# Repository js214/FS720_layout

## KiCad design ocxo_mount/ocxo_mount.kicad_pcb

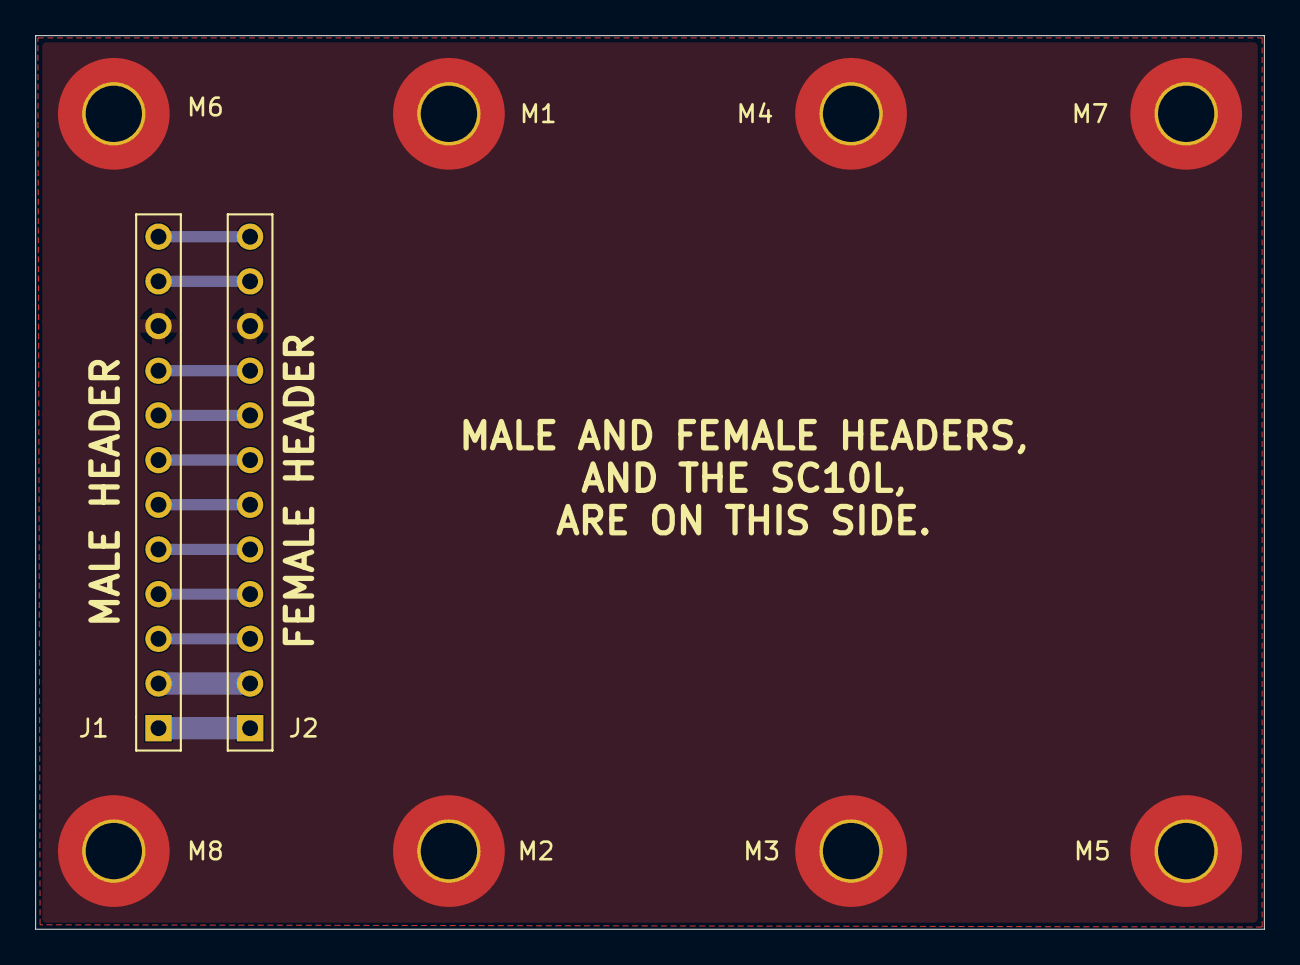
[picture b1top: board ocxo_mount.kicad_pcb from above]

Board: 2 copper layers, 69.8 x 50.8 mm, 10 parts (0 on the bottom side), 12 nets.

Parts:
J1: 12POS 2.54mm; HDR1X12
J2: Conn_01x12; HDR1X12
M1, M2, M3, M4, M5, M6, M7, M8: MountingPad_4-40; Hole_4-40

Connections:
/10MHZ_SINE_OUT: J1.6, J2.6
/10MHZ_SINE_RETURN: J1.7, J2.7
/+5.00VREF_OUT: J1.8, J2.8
/+24VDC: J1.1, J2.1
/AGC_MONITOR: J1.5, J2.5
/AMPL_CTL_IN: J1.11, J2.11
/FREQ_CTL_IN: J1.9, J2.9
/HEATER_POWER_MONITOR: J1.3, J2.3
/POWER_GND: J1.2, J2.2
/TEMP_CTL_IN: J1.12, J2.12
/VARACTOR_MONITOR: J1.4, J2.4
GND: J1.10, J2.10, M1.1 (1_1), M2.1 (1_1), M3.1 (1_1), M4.1 (1_1), M5.1 (1_1), M6.1 (1_1), M7.1 (1_1), M8.1 (1_1)

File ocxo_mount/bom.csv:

"Reference","Qty","Value","DNP","Exclude from BOM","Exclude from Board","Footprint","Datasheet","JLCPCB","SRS PN"
"J1","1","12POS 2.54mm","","","","CONNECTOR_SRS:HDR1X12","","","1-01541"
"J2","1","Conn_01x12","","","","CONNECTOR_SRS:HDR1X12","","","1-01602"
"PCB101","1","PCB","","","Excluded from board","","","--",""
"SC1,SC2,SC3,SC4,SC5,SC6,SC7,SC8","8","4-40X1/4PP","","","Excluded from board","","","","0-00187"
"ST1,ST2,ST3,ST4","4","4-40X5/8 HX F/F","","","Excluded from board","","","","0-00992"

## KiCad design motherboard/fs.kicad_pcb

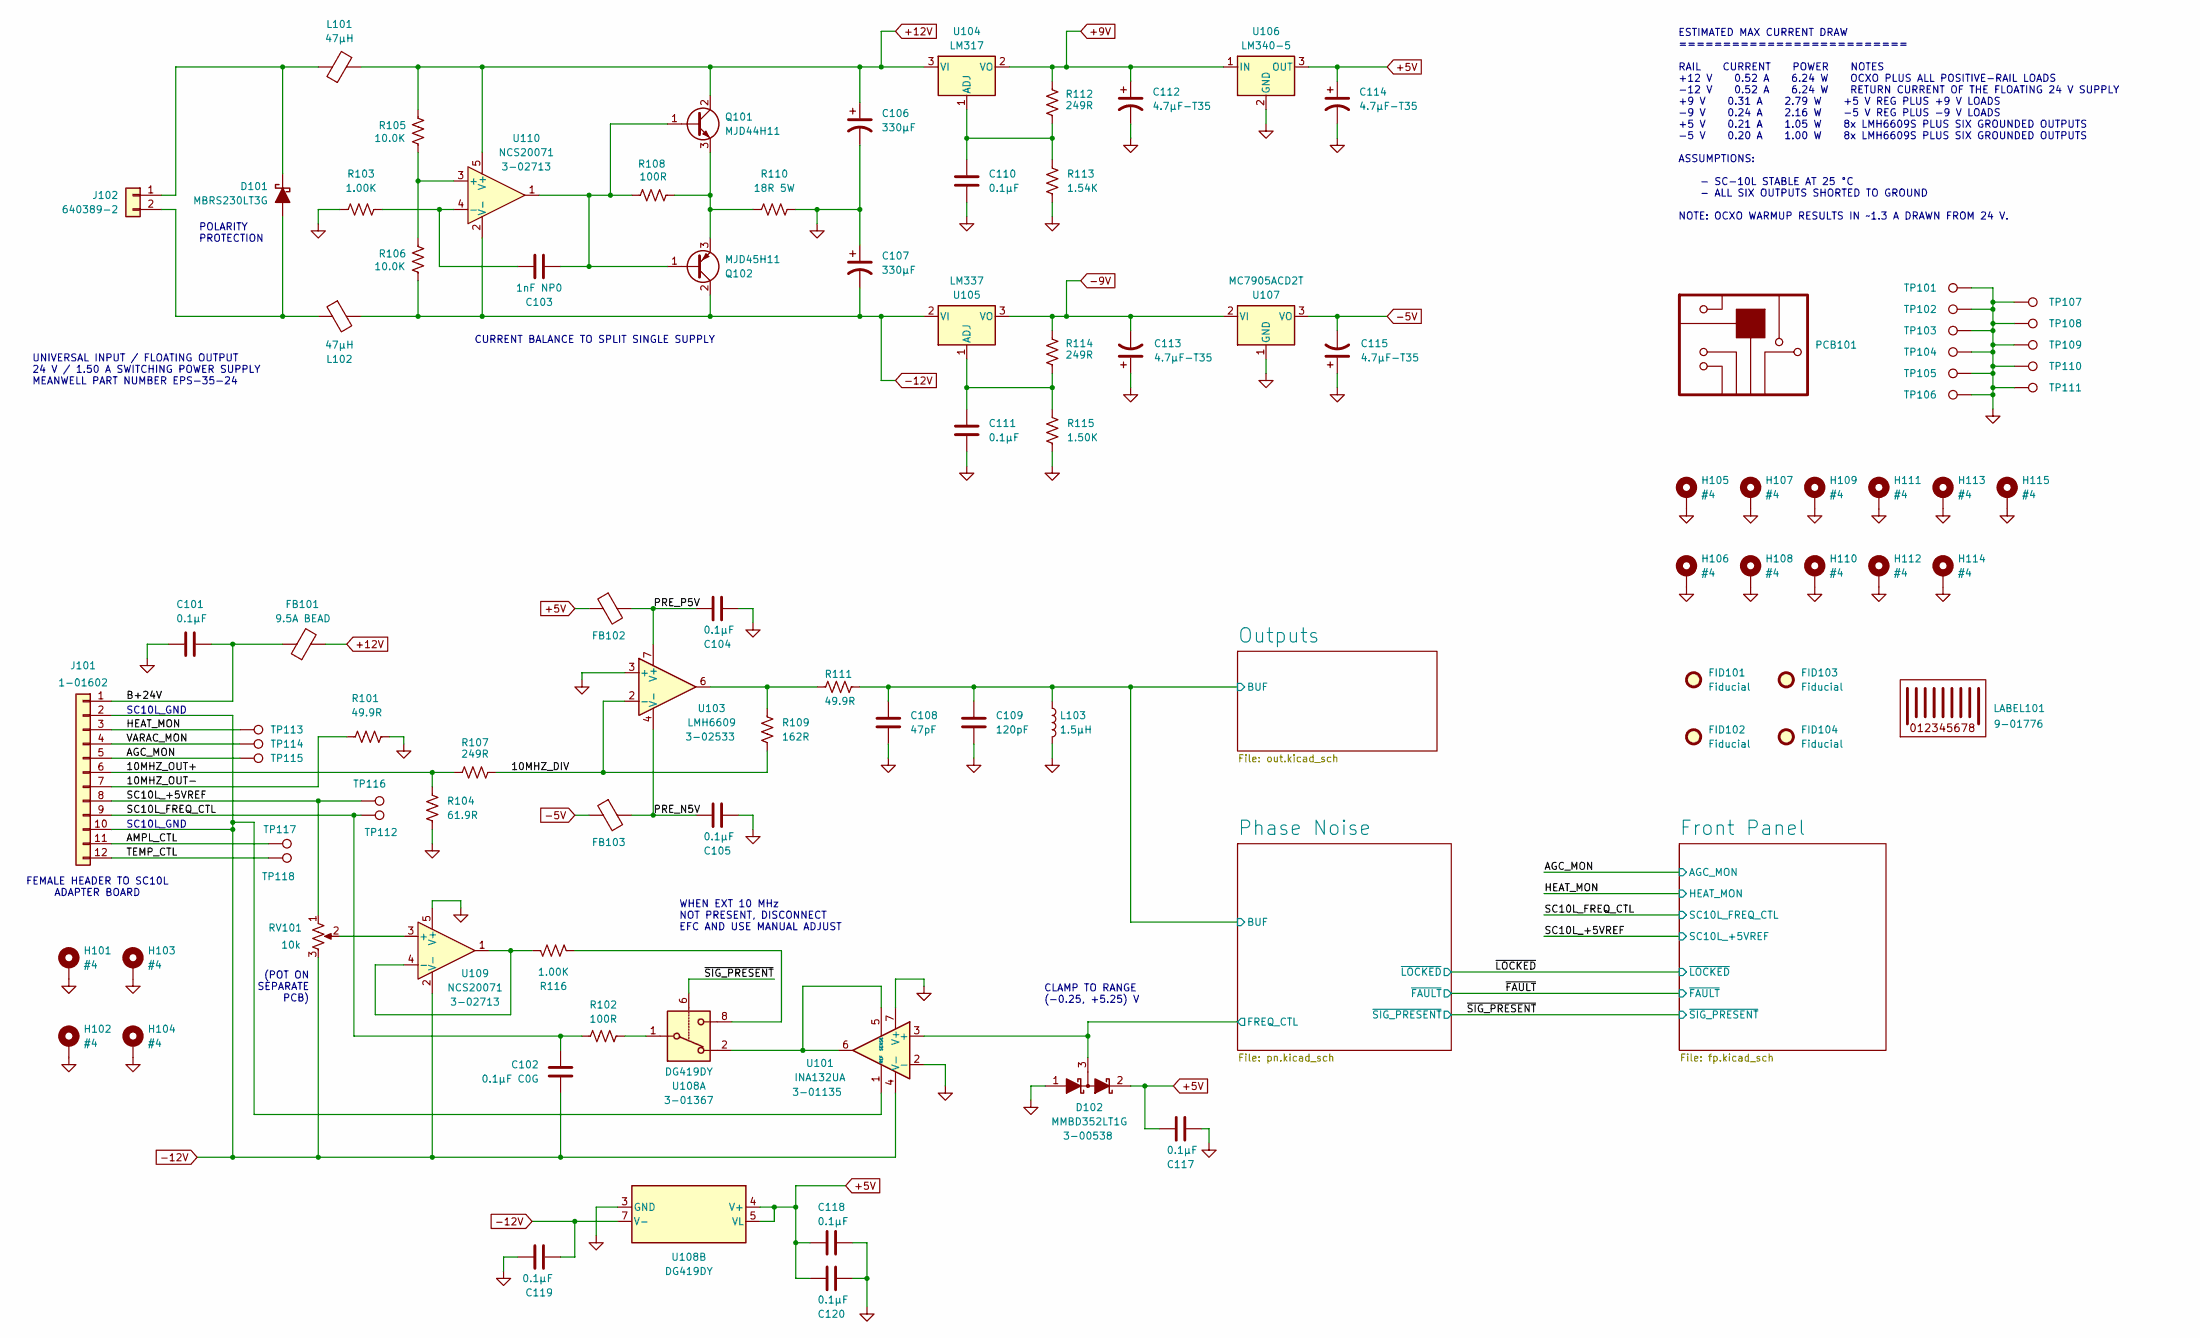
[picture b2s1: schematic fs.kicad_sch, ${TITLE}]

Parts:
C101, C104, C105, C110, C111, C117, C118, C119, C120: 0.1μF; C_0603_1608Metric; Voltage 50V; MPN 06035C104KAT4A; JLCPCB C14663
C102: 0.1μF C0G; C_1206_3216Metric; Voltage 50V; MPN GRT31C5C1H104FA02L; JLCPCB C3839854
C103: 1nF NP0; C_0603_1608Metric; Voltage 50V; MPN C0603C102J5GACTU; JLCPCB C2181873
C106: 330μF; CP_Radial_D10.0mm_P5.00mm; Voltage 35V; MPN EEU-FC1V331; JLCPCB C14745
C107: 330μF; CP_Radial_D10.0mm_P5.00mm; Voltage 35V; MPN EEU-FC1V331; JLCPCB EEU-FC1V331
C108: 47pF; C_0603_1608Metric; Voltage 50V; MPN C0603C470J5GACTU; JLCPCB C2167347
C109: 120pF; C_0603_1608Metric; Voltage 50V; MPN C0603C121J5GACTU; JLCPCB C2168575
C112, C113, C114, C115: 4.7μF-T35; CP_EIA-6032-15_Kemet-U; Voltage 35V; MPN TAJC475M035RNJ; JLCPCB C11378
D101: MBRS230LT3G; D_SMB; MPN MBRS230LT3G; JLCPCB C236135
D102: MMBD352LT1G; SOT-23; MPN MMBD352LT1G; JLCPCB C463549
FB101: 9.5A BEAD; SMB2.5R-2; MPN SMB2.5R-2; JLCPCB C3716465
FB102, FB103: 742863160; L_0603_1608Metric; MPN 742863160; JLCPCB C2650942
FID101, FID102, FID103, FID104: Fiducial; Fiducial_0.5mm_Mask1.5mm; MPN --; JLCPCB --
H101, H102, H103, H104, H105, H106, H107, H108, H109, H110, H111, H112, H113, H114, H115: #4; MountingHole_3.2mm_M3_DIN965_Pad; MPN --; JLCPCB --
J101: Header; PinSocket_1x12_P2.54mm_Vertical; MPN 1-215299-2; JLCPCB C7155422
J102: 640389-2; 640389-2_TYC; MPN 640389-2; JLCPCB C305837
L101, L102: 47μH; PM3316; MPN PM3316-470M-RC; JLCPCB C1329573
L103: 1.5μH; L_0805_2012Metric; MPN MLF2012A1R5JTD25; JLCPCB C76794
LABEL101: Label; LABEL_1in_0.25in; MPN 10011975; JLCPCB --
PCB101: PCB; MPN --; JLCPCB --
Q101: MJD44H11; TO-252-2; MPN MJD44H11G; JLCPCB C36608
Q102: MJD45H11; TO-252-2; MPN MJD45H11G; JLCPCB C5424
R101, R111: 49.9R; R_0603_1608Metric; MPN TFCR0603-16W-E-49R9FT; JLCPCB C23185
R102, R108: 100R; R_0603_1608Metric; MPN RR0816P-101-D; JLCPCB C22775
R103, R116: 1.00K; R_0603_1608Metric; MPN RR0816P-102-D; JLCPCB C22548
R104: 61.9R; R_0603_1608Metric; MPN TFCR0603-16W-E-61R9F; JLCPCB C101138
R105, R106: 10.0K; R_0603_1608Metric; MPN TFCR0603-16W-E-1002FT; JLCPCB C98220
R107, R112, R114: 249R; R_0603_1608Metric; MPN TFCR0603-16W-E-2490FT; JLCPCB C22919
R109: 162R; R_0603_1608Metric; MPN TFCR0603-16W-E-1620F; JLCPCB C185368
R110: 18R 5W; R_Axial_Power_L25.0mm_W9.0mm_P30.48mm; MPN CW00518R00JE12; JLCPCB --
R113: 1.54K; R_0603_1608Metric; MPN TFCR0603-16W-E-1541F; JLCPCB C22842
R115: 1.50K; R_0603_1608Metric; MPN TFCR0603-16W-E-1501FT; JLCPCB C22843
RV101: 10k; PinHeader_1x03_P2.54mm_Vertical
TP101, TP102, TP103, TP104, TP105, TP106, TP107, TP108, TP109, TP110, TP111: TestPoint; TestPoint_THTPad_D2.0mm_Drill1.0mm
TP112, TP113, TP114, TP115, TP116, TP117, TP118: TestPoint; TestPoint_THTPad_D1.0mm_Drill0.5mm; MPN --; JLCPCB --
U101: INA132UA; SO-8_3.9x4.9mm_P1.27mm; MPN INA132UA/2K5; JLCPCB C38199
U103: LMH6609; SO-8_3.9x4.9mm_P1.27mm; MPN LMH6609MAX/NOPB; JLCPCB C2060005
U104: LM317; SOT-223-3_TabPin2; MPN LM317DCYR; JLCPCB C51466
U105: LM337; SOT-223-3_TabPin2; MPN LM337IMPX/NOPB; JLCPCB C74510
U106: LM340-5; TO-263-3_TabPin2; MPN LM340SX-5.0/NOPB; JLCPCB C2870849
U107: MC7905ACD2T; TO-263-2; MPN MC7905ACD2TR4G; JLCPCB C898727
U108: DG419DY; SO-8_3.9x4.9mm_P1.27mm; MPN DG419DY-T1-E3; JLCPCB C6581
U109, U110: NCS20071; TSOT-23-5; MPN NCS20071SN2T1G; JLCPCB C457774

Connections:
+5V: C114.1, C117.2, C118.2, C120.2, D102.2 (K), FB102.1, U106.3 (OUT), U108.4 (V+), U108.5 (VL); also elsewhere on the board
+9V: C112.1, R112.2, U104.2 (VO), U106.1 (IN); also elsewhere on the board
+12V: C106.1, FB101.2, L101.2, Q101.2 (C), R105.1, U104.3 (VI), U110.5 (V+); also elsewhere on the board
-5V: C115.2, FB103.1, U107.3 (VO); also elsewhere on the board
-9V: C113.2, R114.2, U105.3 (VO), U107.2 (VI); also elsewhere on the board
-12V: C102.2, C107.2, C119.2, J101.2, J101.10, L102.2, Q102.2 (C), R106.2, RV101.3, U101.1 (REF), U101.4 (V-), U105.2 (VI), U108.7 (V-), U109.2 (V-), U110.2 (V-); also elsewhere on the board
/10MHZ_DIV: R107.1, R109.2, U103.2 (-)
/10MHZ_OUT+: J101.6, R104.1, R107.2
/10MHZ_OUT-: J101.7, R101.1
/AGC_MON: J101.5, TP115.1 (1_1); also elsewhere on the board
/AMPL_CTL: J101.11, TP117.1 (1_1)
/B+24V: C101.1, FB101.1, J101.1
/HEAT_MON: J101.3, TP113.1 (1_1); also elsewhere on the board
/Outputs/BUF: C108.1, C109.1, L103.1, R111.2; also elsewhere on the board
/PRE_N5V: C105.2, FB103.2, U103.4 (V-)
/PRE_P5V: C104.2, FB102.2, U103.7 (V+)
/Phase Noise/FREQ_CTL: D102.3 (COM), U101.3 (+); also elsewhere on the board
/SC10L_+5VREF: J101.8, RV101.1, TP116.1 (1_1); also elsewhere on the board
/SC10L_FREQ_CTL: C102.1, J101.9, R102.1, TP112.1 (1_1); also elsewhere on the board
/TEMP_CTL: J101.12, TP118.1 (1_1)
/VARAC_MON: J101.4, TP114.1 (1_1)
/~SIG_PRESENT: U108.6; also elsewhere on the board
GND: C101.2, C104.1, C105.1, C106.2, C107.1, C108.2, C109.2, C110.1, C111.1, C112.2, C113.1, C114.2, C115.1, C117.1, C118.1, C119.1, C120.1, D102.1 (A), H101.1 (1_1), H102.1 (1_1), H103.1 (1_1), H104.1 (1_1), H105.1 (1_1), H106.1 (1_1), H107.1 (1_1), H108.1 (1_1), H109.1 (1_1), H110.1 (1_1), H111.1 (1_1), H112.1 (1_1), H113.1 (1_1), H114.1 (1_1), H115.1 (1_1), L103.2, R101.2, R103.1, R104.2, R110.2, R113.2, R115.2, TP101.1 (1_1), TP102.1 (1_1), TP103.1 (1_1), TP104.1 (1_1), TP105.1 (1_1), TP106.1 (1_1), TP107.1 (1_1), TP108.1 (1_1), TP109.1 (1_1), TP110.1 (1_1), TP111.1 (1_1), U101.2 (-), U101.7 (V+), U103.3 (+), U106.2 (GND), U107.1 (GND), U108.3 (GND), U109.5 (V+); also elsewhere on the board
unnamed: D101.2 (A), J102.2, L102.1
unnamed: D101.1 (K), J102.1, L101.1
unnamed: C103.2, Q101.1 (B), Q102.1 (B), R108.2, U110.1
unnamed: Q101.3 (E), Q102.3 (E), R108.1, R110.1
unnamed: R102.2, U108.1
unnamed: R109.1, R111.1, U103.6
unnamed: R116.2, U108.8
unnamed: U101.5 (SENSE), U101.6, U108.2
unnamed: C110.2, R112.1, R113.1, U104.1 (ADJ)
unnamed: C111.2, R114.1, R115.1, U105.1 (ADJ)
unnamed: RV101.2, U109.3 (+)
unnamed: R116.1, U109.1, U109.4 (-)
unnamed: R105.2, R106.1, U110.3 (+)
unnamed: C103.1, R103.2, U110.4 (-)

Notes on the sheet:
SC10L_GND
WHEN EXT 10 MHz NOT PRESENT, DISCONNECT EFC AND USE MANUAL ADJUST
ESTIMATED MAX CURRENT DRAW ========================== RAIL CURRENT POWER NOTES +12 V 0.52 A 6.24 W OCXO PLUS ALL POSITIVE-RAIL LOADS −12 V 0.52 A 6.24 W RETURN CURRENT OF THE FLOATING 24 V SUPPLY +9 V 0.31 A 2.79 W +5 V REG PLUS +9 V LOADS −9 V 0.24 A 2.16 W −5 V REG PLUS −9 V LOADS +5 V 0.21 A 1.0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
FEMALE HEADER TO SC10L ADAPTER BOARD
CURRENT BALANCE TO SPLIT SINGLE SUPPLY
(POT ON SEPARATE PCB)
POLARITY PROTECTION
UNIVERSAL INPUT / FLOATING OUTPUT 24 V / 1.50 A SWITCHING POWER SUPPLY MEANWELL PART NUMBER EPS-35-24
CLAMP TO RANGE (−0.25, +5.25) V

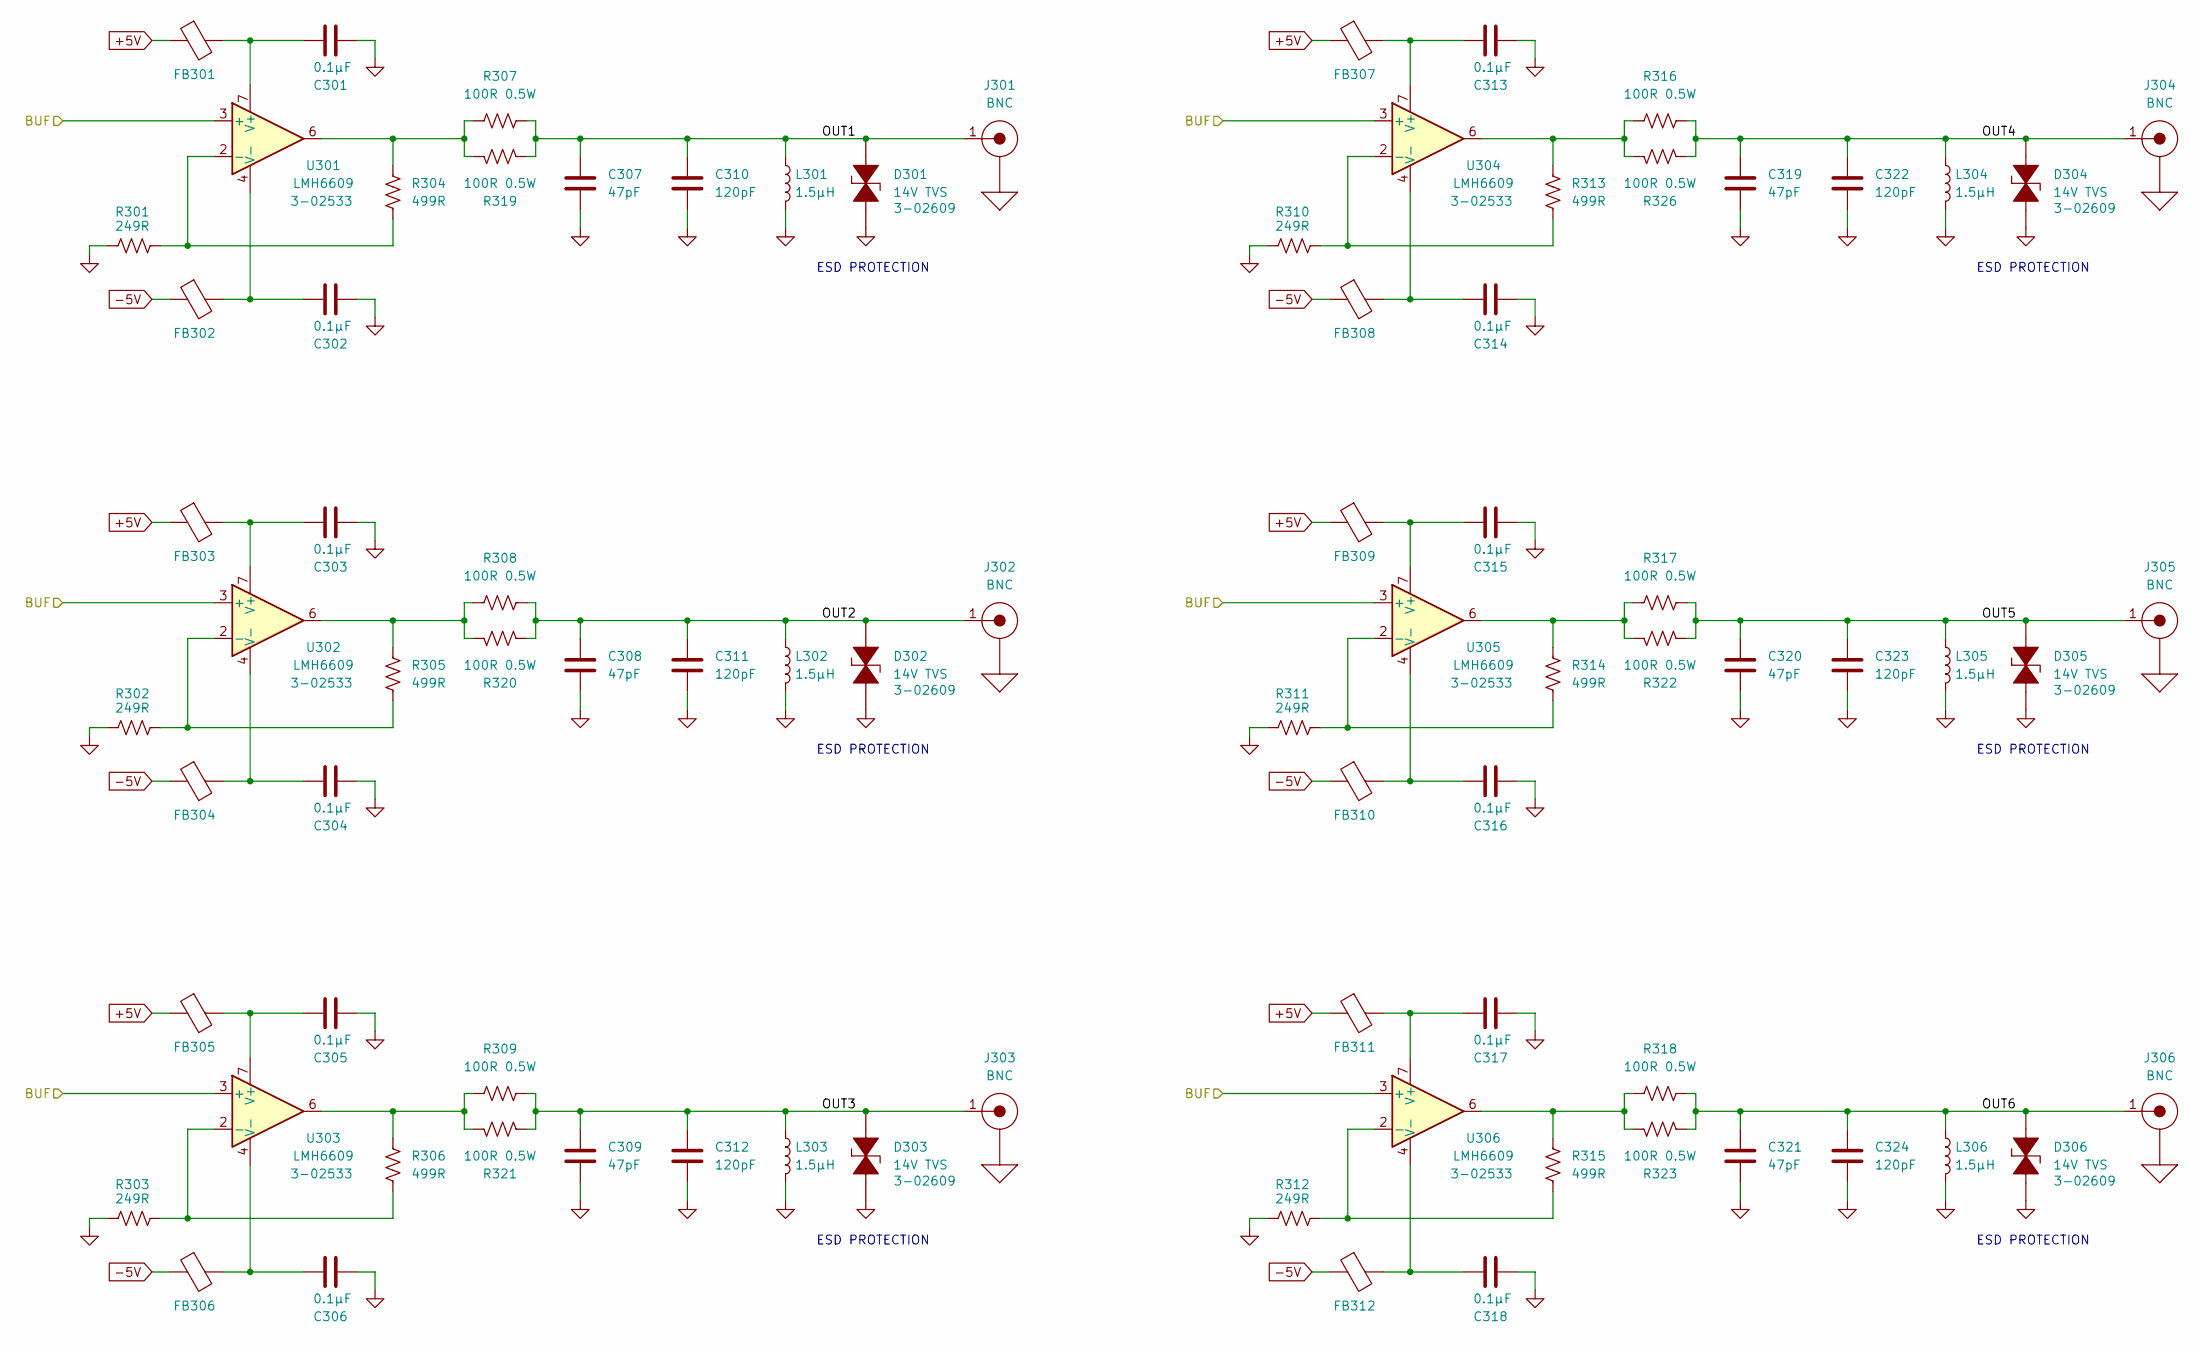
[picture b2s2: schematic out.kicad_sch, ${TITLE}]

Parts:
C301, C302, C303, C304, C305, C306, C313, C314, C315, C316, C317, C318: 0.1μF; C_0603_1608Metric; Voltage 50V; MPN 06035C104KAT4A; JLCPCB C14663
C307, C308, C309, C319, C320, C321: 47pF; C_0603_1608Metric; Voltage 50V; MPN C0603C470J5GACTU; JLCPCB C2167347
C310, C311, C312, C322, C323, C324: 120pF; C_0603_1608Metric; Voltage 50V; MPN C0603C121J5GACTU; JLCPCB C2168575
D301, D302, D303, D304, D305, D306: 14V TVS; C_0402_1005Metric; MPN PESD0402-140; JLCPCB C7473167
FB301, FB302, FB303, FB304, FB305, FB306, FB307, FB308, FB309, FB310, FB311, FB312: 742863160; L_0603_1608Metric; MPN 742863160; JLCPCB C2650942
J301, J302, J303, J304, J305, J306: BNC; BNC-STRIP; MPN 73100-0195; JLCPCB --
L301, L302, L303, L304, L305, L306: 1.5μH; L_0805_2012Metric; MPN MLF2012A1R5JTD25; JLCPCB C139220
R301, R302, R303, R310, R311, R312: 249R; R_0603_1608Metric; MPN TFCR0603-16W-E-2490FT; JLCPCB C22919
R304, R305, R306, R313, R314, R315: 499R; R_0603_1608Metric; MPN TFCR0603-16W-E-4990FT; JLCPCB C23065
R307, R308, R309, R316, R317, R318, R319, R320, R321, R322, R323, R326: 100R 0.5W; R_1206_3216Metric; MPN RNCP1206FTD100R; JLCPCB C2441432
U301, U302, U303, U304, U305, U306: LMH6609; SO-8_3.9x4.9mm_P1.27mm; MPN LMH6609MAX/NOPB; JLCPCB C2060005

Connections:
+5V: FB301.1, FB303.1, FB305.1, FB307.1, FB309.1, FB311.1; also elsewhere on the board
-5V: FB302.1, FB304.1, FB306.1, FB308.1, FB310.1, FB312.1; also elsewhere on the board
/Outputs/BUF: U301.3 (+), U302.3 (+), U303.3 (+), U304.3 (+), U305.3 (+), U306.3 (+); also elsewhere on the board
/Outputs/OUT1: C307.1, C310.1, D301.1 (CATHODE), J301.1 (C_1), L301.1, R307.2, R319.2
/Outputs/OUT2: C308.1, C311.1, D302.1 (CATHODE), J302.1 (C_1), L302.1, R308.2, R320.2
/Outputs/OUT3: C309.1, C312.1, D303.1 (CATHODE), J303.1 (C_1), L303.1, R309.2, R321.2
/Outputs/OUT4: C319.1, C322.1, D304.1 (CATHODE), J304.1 (C_1), L304.1, R316.2, R326.2
/Outputs/OUT5: C320.1, C323.1, D305.1 (CATHODE), J305.1 (C_1), L305.1, R317.2, R322.2
/Outputs/OUT6: C321.1, C324.1, D306.1 (CATHODE), J306.1 (C_1), L306.1, R318.2, R323.2
GND: C301.1, C302.1, C303.1, C304.1, C305.1, C306.1, C307.2, C308.2, C309.2, C310.2, C311.2, C312.2, C313.1, C314.1, C315.1, C316.1, C317.1, C318.1, C319.2, C320.2, C321.2, C322.2, C323.2, C324.2, D301.2 (ANODE), D302.2 (ANODE), D303.2 (ANODE), D304.2 (ANODE), D305.2 (ANODE), D306.2 (ANODE), L301.2, L302.2, L303.2, L304.2, L305.2, L306.2, R301.2, R302.2, R303.2, R310.2, R311.2, R312.2; also elsewhere on the board
unnamed: R304.1, R307.1, R319.1, U301.6
unnamed: R305.1, R308.1, R320.1, U302.6
unnamed: R306.1, R309.1, R321.1, U303.6
unnamed: R313.1, R316.1, R326.1, U304.6
unnamed: R314.1, R317.1, R322.1, U305.6
unnamed: R315.1, R318.1, R323.1, U306.6
unnamed: R301.1, R304.2, U301.2 (-)
unnamed: C301.2, FB301.2, U301.7 (V+)
unnamed: C302.2, FB302.2, U301.4 (V-)
unnamed: R302.1, R305.2, U302.2 (-)
unnamed: C303.2, FB303.2, U302.7 (V+)
unnamed: C304.2, FB304.2, U302.4 (V-)
unnamed: R303.1, R306.2, U303.2 (-)
unnamed: C305.2, FB305.2, U303.7 (V+)
unnamed: C306.2, FB306.2, U303.4 (V-)
unnamed: R310.1, R313.2, U304.2 (-)
unnamed: C313.2, FB307.2, U304.7 (V+)
unnamed: C314.2, FB308.2, U304.4 (V-)
unnamed: R311.1, R314.2, U305.2 (-)
unnamed: C315.2, FB309.2, U305.7 (V+)
unnamed: C316.2, FB310.2, U305.4 (V-)
unnamed: R312.1, R315.2, U306.2 (-)
unnamed: C317.2, FB311.2, U306.7 (V+)
unnamed: C318.2, FB312.2, U306.4 (V-)

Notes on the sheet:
ESD PROTECTION

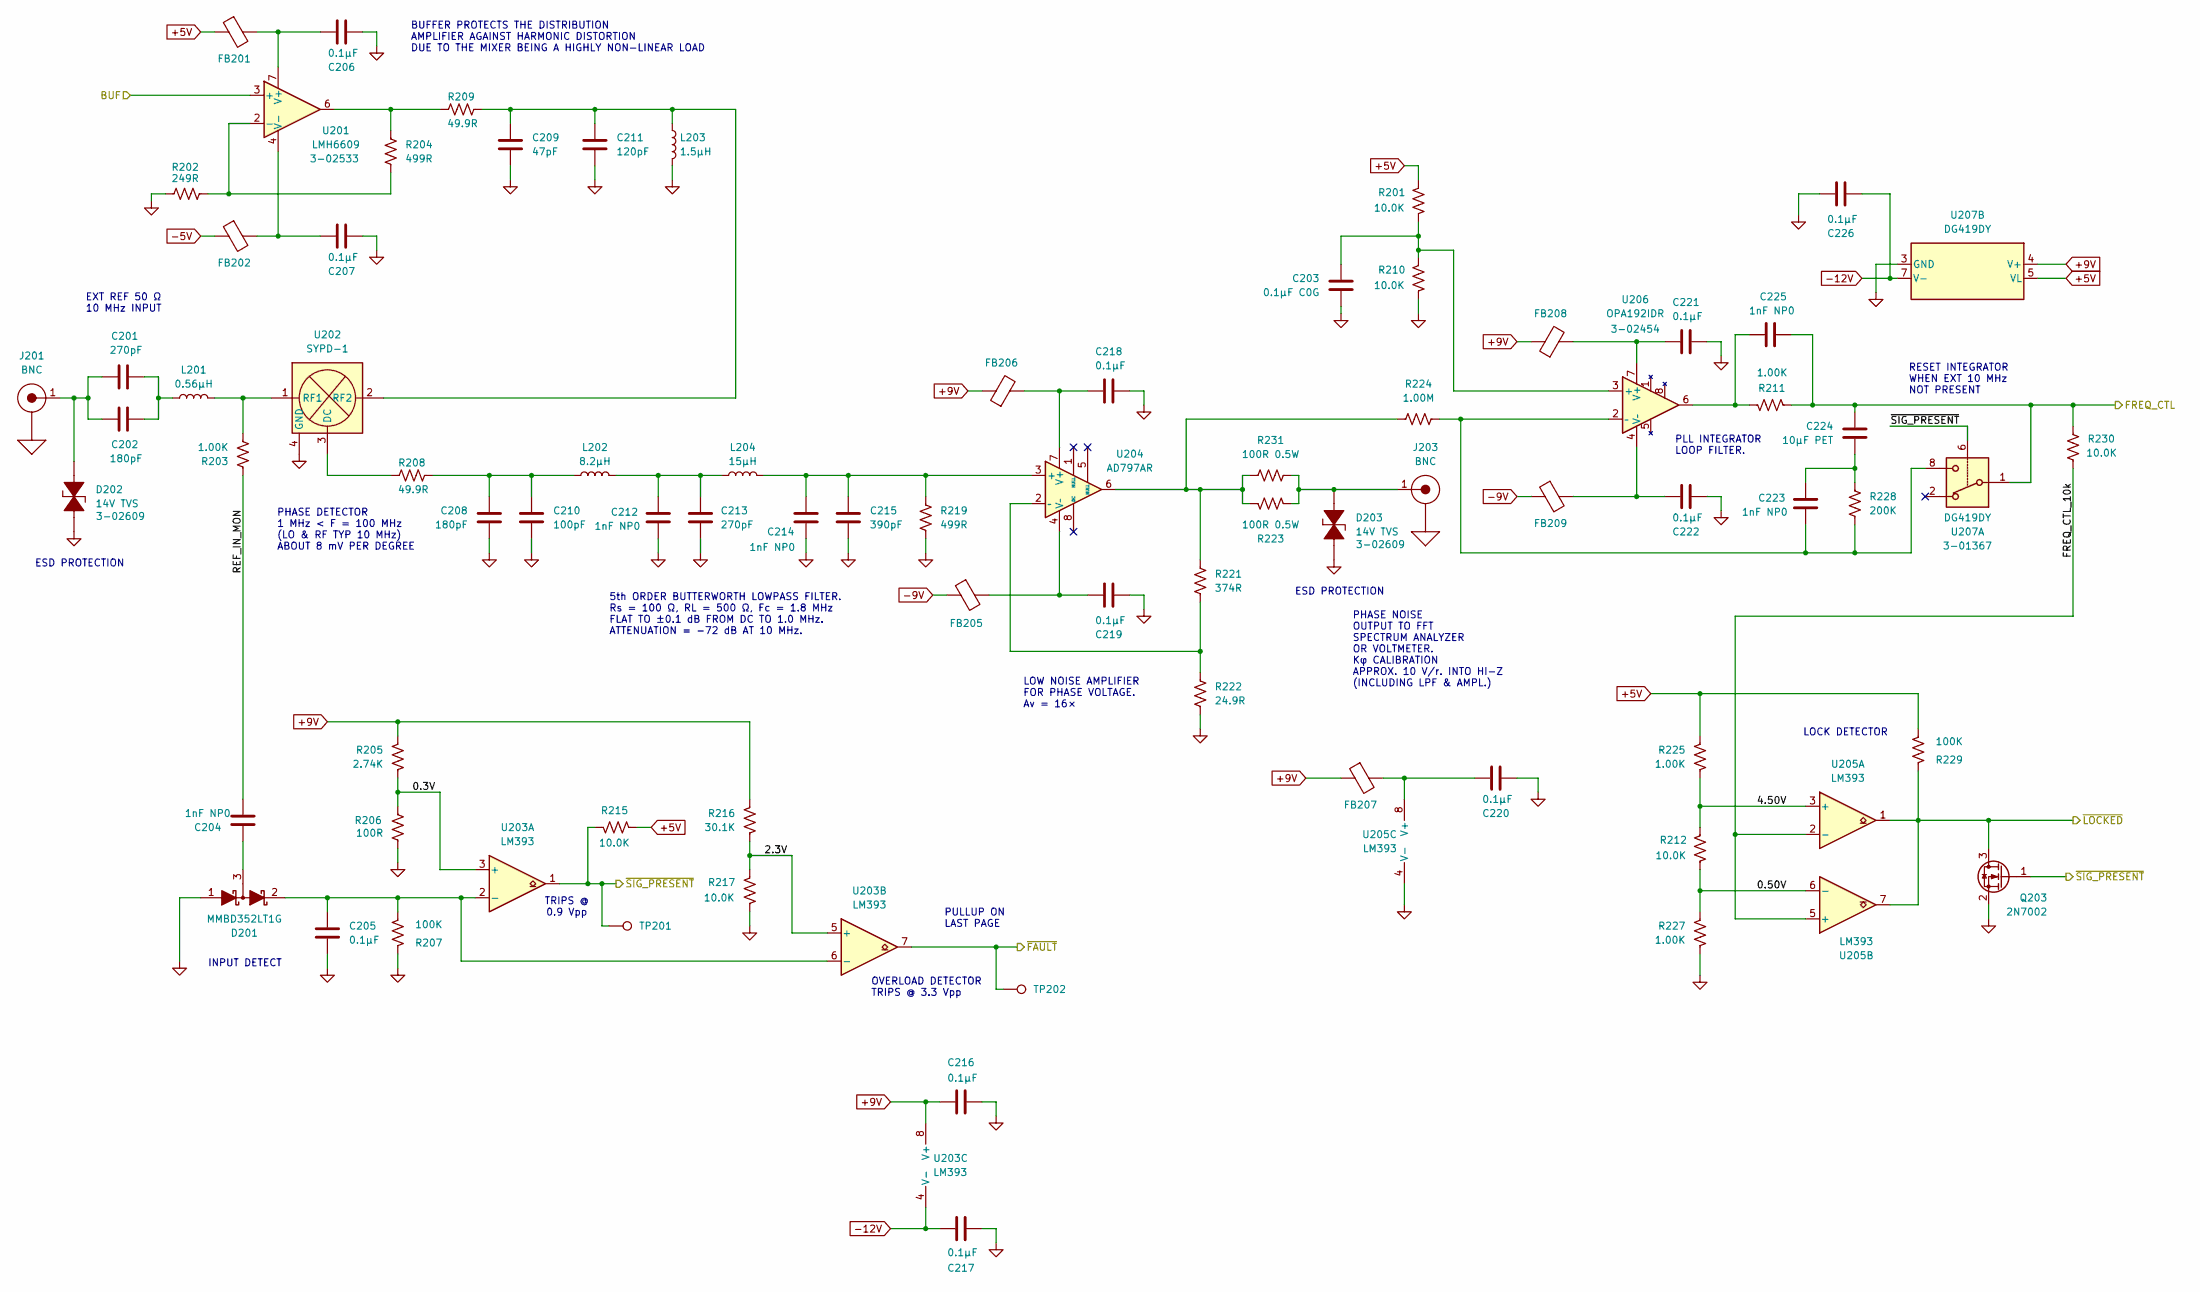
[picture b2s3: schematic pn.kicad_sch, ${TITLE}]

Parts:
C201, C213: 270pF; C_0603_1608Metric; Voltage 50V; MPN C0603C271J5GACTU; JLCPCB C49326315
C202, C208: 180pF; C_1206_3216Metric; Voltage 50V; MPN C1206C181J5GACTU; JLCPCB C541494
C203: 0.1μF C0G; C_1206_3216Metric; Voltage 50V; MPN GRT31C5C1H104FA02L; JLCPCB C3839854
C204, C212, C214, C223, C225: 1nF NP0; C_0603_1608Metric; Voltage 50V; MPN C0603C102J5GACTU; JLCPCB C2181873
C205, C206, C207, C216, C217, C218, C219, C220, C221, C222, C226: 0.1μF; C_0603_1608Metric; Voltage 50V; MPN 06035C104KAT4A; JLCPCB C14663
C209: 47pF; C_0603_1608Metric; Voltage 50V; MPN C0603C470J5GACTU; JLCPCB C2167347
C210: 100pF; C_0603_1608Metric; Voltage 50V; MPN C0603C101J5GACTU; JLCPCB C2167328
C211: 120pF; C_0603_1608Metric; Voltage 50V; MPN C0603C121J5GACTU; JLCPCB C2168575
C215: 390pF; C_0603_1608Metric; Voltage 50V; MPN C0603C391J5GACTU; JLCPCB C22408867
C224: 10μF PET; C_Rect_L18.0mm_W9.0mm_P15.00mm_FKS3_FKP3; Voltage 63V; MPN B32522C0106K189; JLCPCB C3769153
D201: MMBD352LT1G; SOT-23; MPN MMBD352LT1G; JLCPCB C463549
D202, D203: 14V TVS; C_0402_1005Metric; MPN PESD0402-140; JLCPCB C7473167
FB201, FB202, FB205, FB206, FB207, FB208, FB209: 742863160; L_0603_1608Metric; MPN 742863160; JLCPCB C2650942
J201, J203: BNC; BNC-STRIP; MPN 73100-0195; JLCPCB --
L201: 0.56μH; L_1210_3225Metric; MPN 1206CS-561XJRC; JLCPCB C318049
L202: 8.2μH; L_1206_3216Metric; MPN AIML-1206-8R2K-T; JLCPCB C51018442
L203: 1.5μH; L_0805_2012Metric; MPN MLF2012A1R5JTD25; JLCPCB C139220
L204: 15μH; L_0805_2012Metric; MPN MLF2012C150K; JLCPCB C383402
Q203: 2N7002; SOT-23; MPN 2N7002H6327XTSA2; JLCPCB C8545
R201, R210, R212, R215, R217, R230: 10.0K; R_0603_1608Metric; MPN TFCR0603-16W-E-1002FT; JLCPCB C98220
R202: 249R; R_0603_1608Metric; MPN TFCR0603-16W-E-2490FT; JLCPCB C22919
R203, R211, R225, R227: 1.00K; R_0603_1608Metric; MPN RR0816P-102-D; JLCPCB C22548
R204, R219: 499R; R_0603_1608Metric; MPN TFCR0603-16W-E-4990FT; JLCPCB C23065
R205: 2.74K; R_0603_1608Metric; MPN TFCR0603-16W-E-2741FT; JLCPCB C2930073
R206: 100R; R_0603_1608Metric; MPN RR0816P-101-D; JLCPCB C22775
R207, R229: 100K; R_0603_1608Metric; MPN TFCR0603-16W-E-1003FT; JLCPCB C25803
R208, R209: 49.9R; R_0603_1608Metric; MPN TFCR0603-16W-E-49R9FT; JLCPCB C23185
R216: 30.1K; R_0603_1608Metric; MPN RR0816P-3012-D-47C; JLCPCB C23000
R221: 374R; R_0603_1608Metric; MPN TFCR0603-16W-E-3740F; JLCPCB C3981304
R222: 24.9R; R_0603_1608Metric; MPN TFCR0603-16W-E-24R9FT; JLCPCB C22916
R223, R231: 100R 0.5W; R_1206_3216Metric; MPN RNCP1206FTD100R; JLCPCB C2441432
R224: 1.00M; R_0603_1608Metric; MPN RMCF0603FT1M00; JLCPCB C22935
R228: 200K; R_0603_1608Metric; MPN TFCR0603-16W-E-2003FT; JLCPCB C25811
TP201, TP202: TestPoint; TestPoint_THTPad_D1.0mm_Drill0.5mm; MPN --; JLCPCB --
U201: LMH6609; SO-8_3.9x4.9mm_P1.27mm; MPN LMH6609MAX/NOPB; JLCPCB C2060005
U202: SYPD-1; Mini-Circuits_TTT167_LandPatternPL-079; MPN SYPD-1+; JLCPCB C5368969
U203, U205: LM393; SO-8_3.9x4.9mm_P1.27mm; MPN LM393DR; JLCPCB C67470
U204: AD797AR; SO-8_3.9x4.9mm_P1.27mm; MPN AD797ARZ; JLCPCB C578574
U206: OPA192IDR; SOIC-8_3.9x4.9mm_P1.27mm; MPN OPA192IDR; JLCPCB C2861286
U207: DG419DY; SO-8_3.9x4.9mm_P1.27mm; MPN DG419DY-T1-E3; JLCPCB C6581

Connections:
+5V: FB201.1, R201.2, R215.2, R225.2, R229.2, U207.5 (VL); also elsewhere on the board
+9V: C216.2, FB206.1, FB207.1, FB208.1, R205.1, R216.2, U203.8 (V+), U207.4 (V+); also elsewhere on the board
-5V: FB202.1; also elsewhere on the board
-9V: FB205.1, FB209.1; also elsewhere on the board
-12V: C217.2, C226.1, U203.4 (V-), U207.7 (V-); also elsewhere on the board
/Outputs/BUF: U201.3 (+); also elsewhere on the board
/Phase Noise/0.3V: R205.2, R206.1, U203.3 (+)
/Phase Noise/0.50V: R212.1, R227.2, U205.6 (-)
/Phase Noise/2.3V: R216.1, R217.2, U203.5 (+)
/Phase Noise/4.50V: R212.2, R225.1, U205.3 (+)
/Phase Noise/FREQ_CTL: C224.1, C225.1, R211.2, R230.2, U207.1; also elsewhere on the board
/Phase Noise/FREQ_CTL_10k: R230.1, U205.2 (-), U205.5 (+)
/Phase Noise/REF_IN_MON: C204.1, R203.2
/~FAULT: TP202.1 (1_1), U203.7; also elsewhere on the board
/~LOCKED: Q203.3 (D), R229.1, U205.1, U205.7; also elsewhere on the board
/~SIG_PRESENT: Q203.1 (G), R215.1, TP201.1 (1_1), U203.1, U207.6; also elsewhere on the board
GND: C203.2, C205.1, C206.1, C207.1, C208.2, C209.2, C210.2, C211.2, C212.1, C213.2, C214.1, C215.2, C216.1, C217.1, C218.1, C219.1, C220.1, C221.1, C222.1, C226.2, D201.1 (A), D202.2 (ANODE), D203.2 (ANODE), L203.2, Q203.2 (S), R202.2, R206.2, R207.1, R210.1, R217.1, R219.1, R222.2, R227.1, U202.4 (GND), U202.5 (GND), U202.6 (GND), U205.4 (V-), U207.3 (GND); also elsewhere on the board
unnamed: C201.2, C202.2, L201.1
unnamed: C208.1, C210.1, L202.1, R208.2
unnamed: C212.2, C213.1, L202.2, L204.1
unnamed: C223.2, C224.2, R228.1
unnamed: C225.2, R211.1, U206.6
unnamed: C204.2, D201.3 (COM)
unnamed: C205.2, D201.2 (K), R207.2, U203.2 (-), U203.6 (-)
unnamed: C201.1, C202.1, D202.1 (CATHODE), J201.1 (C_1)
unnamed: D203.1 (CATHODE), J203.1 (C_1), R223.2, R231.2
unnamed: R204.1, R209.1, U201.6
unnamed: R221.1, R223.1, R224.1, R231.1, U204.6
unnamed: R202.1, R204.2, U201.2 (-)
unnamed: C206.2, FB201.2, U201.7 (V+)
unnamed: C207.2, FB202.2, U201.4 (V-)
unnamed: R208.1, U202.3 (DC)
unnamed: L201.2, R203.1, U202.1 (RF1)
unnamed: C209.1, C211.1, L203.1, R209.2, U202.2 (RF2)
unnamed: C214.2, C215.1, L204.2, R219.2, U204.3 (+)
unnamed: C218.2, FB206.2, U204.7 (V+)
unnamed: C219.2, FB205.2, U204.4 (V–)
unnamed: R221.2, R222.1, U204.2 (–)
unnamed: C220.2, FB207.2, U205.8 (V+)
unnamed: C203.1, R201.1, R210.2, U206.3 (+)
unnamed: C221.2, FB208.2, U206.7 (V+)
unnamed: C222.2, FB209.2, U206.4 (V–)
unnamed: C223.1, R224.2, R228.2, U206.2 (–), U207.8

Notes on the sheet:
RESET INTEGRATOR WHEN EXT 10 MHz NOT PRESENT
5th ORDER BUTTERWORTH LOWPASS FILTER. Rs = 100 Ω, RL = 500 Ω, Fc = 1.8 MHz FLAT TO ±0.1 dB FROM DC TO 1.0 MHz. ATTENUATION = -72 dB AT 10 MHz.
PHASE DETECTOR 1 MHz < F = 100 MHz (LO & RF TYP 10 MHz) ABOUT 8 mV PER DEGREE
PULLUP ON LAST PAGE
ESD PROTECTION
TRIPS @ 0.9 Vpp
EXT REF 50 Ω 10 MHz INPUT
PHASE NOISE OUTPUT TO FFT SPECTRUM ANALYZER OR VOLTMETER. Kφ CALIBRATION APPROX. 10 V/r. INTO HI-Z (INCLUDING LPF & AMPL.)
INPUT DETECT
BUFFER PROTECTS THE DISTRIBUTION AMPLIFIER AGAINST HARMONIC DISTORTION DUE TO THE MIXER BEING A HIGHLY NON-LINEAR LOAD
LOW NOISE AMPLIFIER FOR PHASE VOLTAGE. Av = 16×
OVERLOAD DETECTOR TRIPS @ 3.3 Vpp
PLL INTEGRATOR LOOP FILTER.
LOCK DETECTOR
